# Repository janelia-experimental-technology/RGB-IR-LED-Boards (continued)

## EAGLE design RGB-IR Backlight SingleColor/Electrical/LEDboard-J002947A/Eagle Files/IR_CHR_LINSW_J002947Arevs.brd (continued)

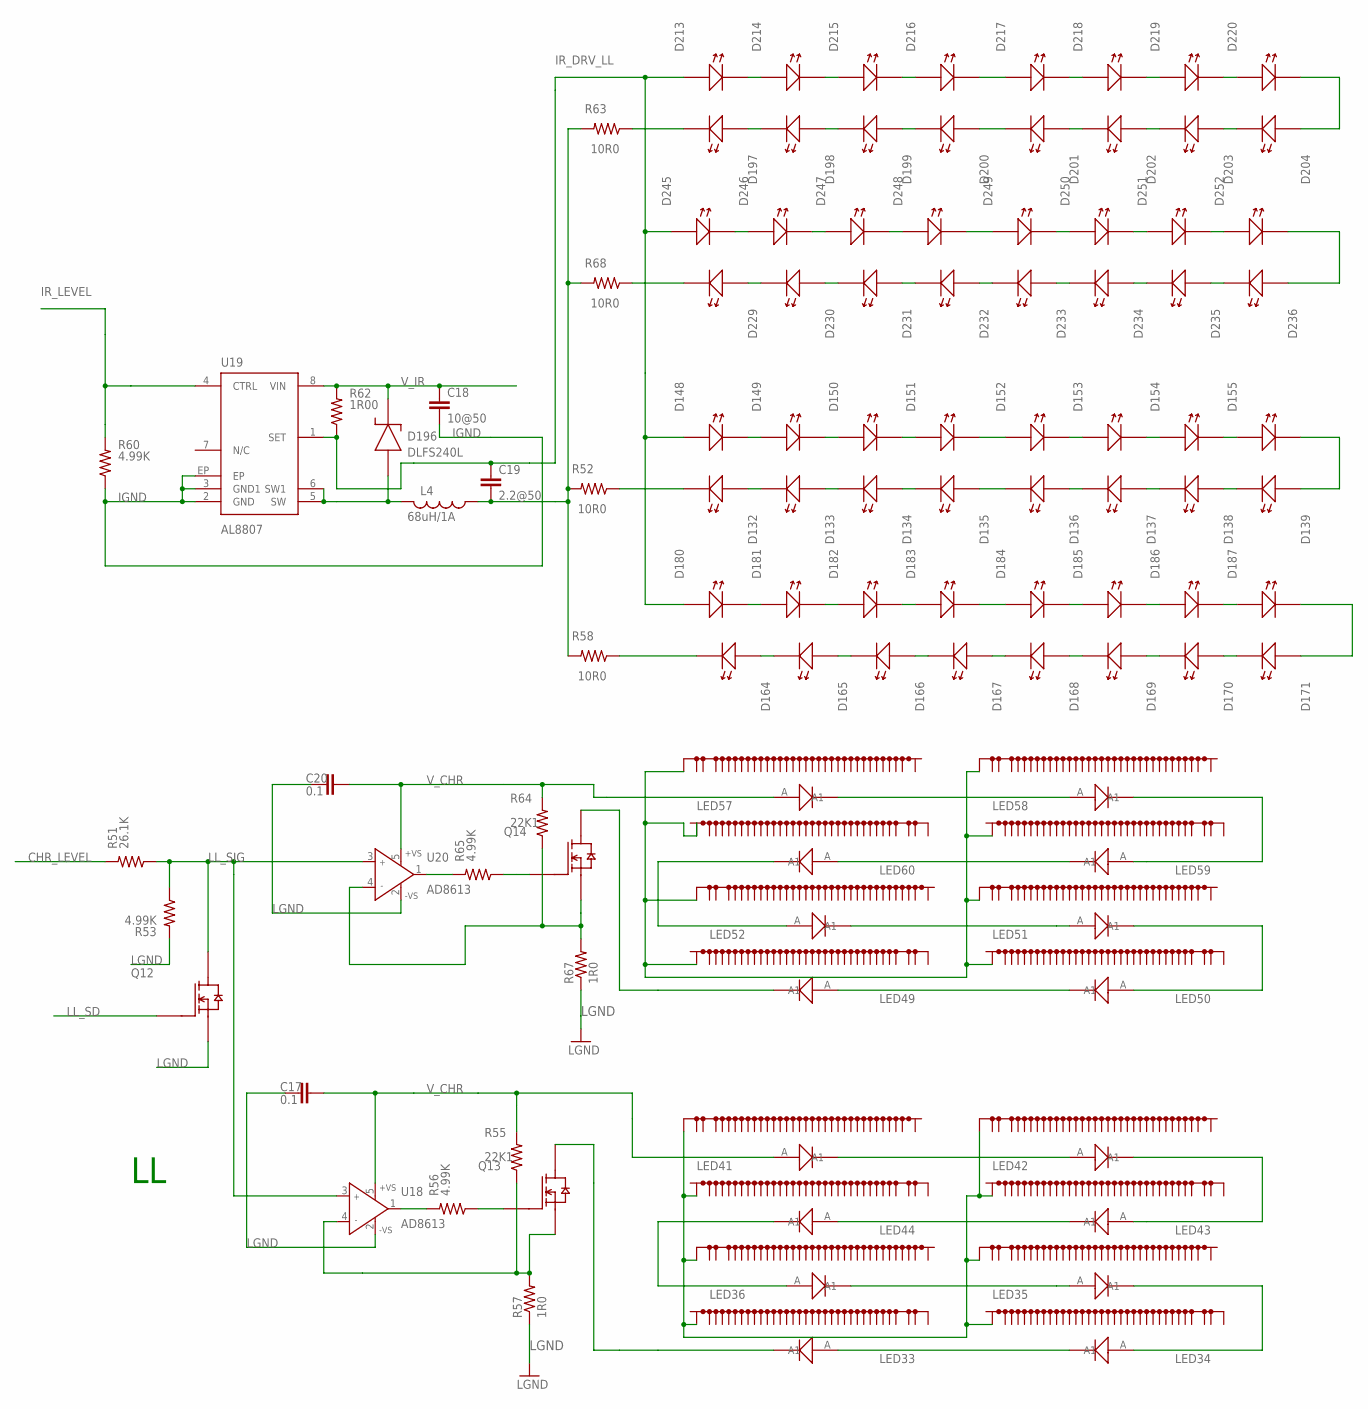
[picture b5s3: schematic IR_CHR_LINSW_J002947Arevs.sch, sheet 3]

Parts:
C17, C20: 0.1; 0603S
C18: 10@50; 1206S
C19: 2.2@50; 1206S
D132, D133, D134, D135, D136, D137, D138, D148, D149, D150, D151, D152, D153, D154, D155, D164, D165, D166, D167, D168, D169, D170, D171, D180, D181, D182, D183, D184, D185, D186, D187, D197, D198, D199, D200, D201, D202, D203, D204, D213, D214, D215, D216, D217, D218, D219, D220, D229, D230, D231, D232, D233, D234, D235, D236, D245, D246, D247, D248, D249, D250, D251, D252: LEDLED_SFH4050_HEAT; LED_SFH4050_HEAT
D139: LEDLED_SFH4050_C; LED_SFH4050_HEAT_C
D196: DLFS240L; PWRDI-123
L4: 68uH/1A; SRU8043
LED33, LED34, LED35, LED36, LED41, LED42, LED43, LED44, LED49, LED50, LED51, LED52, LED57, LED58, LED59, LED60: REBEL_0603OG_LED_W0603_EVEN_12; OG_LED_W0603_EVEN_12
Q12: MOSFET-N; SC-70
Q13, Q14: MOSFET-NTI252_HS; TO252_HS
R51: 26.1K; 0603S
R52, R58, R63, R68: 10R0; 1206S
R53, R56, R65: 4.99K; 0603S
R55, R64: 22K1; 0805S
R57, R67: 1R0; 2512WIDE_HS1
R60: 4.99K; 0805S
R62: 1R00; 1206S
U18, U20: AD8613; SOT23-5
U19: AL8807; MSOP8-EP

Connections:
CHR_LEVEL: R51.2; also elsewhere on the board
IGND: C18.2, R60.1, U19.2 (GND), U19.3 (GND1), U19.EP; also elsewhere on the board
IR_DRV_LL: C19.1, D148.A, D148.A1 (A), D180.A, D180.A1 (A), D213.A, D213.A1 (A), D245.A, D245.A1 (A), R62.1, U19.1 (SET)
IR_LEVEL: R60.2, U19.4 (CTRL); also elsewhere on the board
IR_RET_LL: C19.2, L4.1, R52.2, R58.2, R63.2, R68.2
LGND: C17.2, C20.2, Q12.2 (S), R53.2, R57.1, R57.1A (1), R57.1A1 (1), R57.1B (1), R57.1B1 (1), R57.1C (1), R67.1, R67.1A (1), R67.1A1 (1), R67.1B (1), R67.1B1 (1), R67.1C (1), U18.2 (-VS), U20.2 (-VS); also elsewhere on the board
LL_SD: Q12.1 (G); also elsewhere on the board
LL_SIG: Q12.3 (D), R51.1, R53.1, U18.3 (IN+), U20.3 (IN+)
unnamed: D196.A, L4.2, U19.5 (SW), U19.6 (SW1)
unnamed: D203.A, D203.A1 (A), D204.C (K), D204.C1 (K)
unnamed: Q14.1 (G), R65.1
unnamed: D202.A, D202.A1 (A), D203.C (K), D203.C1 (K)
unnamed: Q13.1 (G), R56.1
unnamed: R65.2, U20.1 (OUT)
unnamed: D201.A, D201.A1 (A), D202.C (K), D202.C1 (K)
unnamed: D199.A, D199.A1 (A), D200.C (K), D200.C1 (K)
unnamed: D198.A, D198.A1 (A), D199.C (K), D199.C1 (K)
unnamed: D197.A, D197.A1 (A), D198.C (K), D198.C1 (K)
unnamed: D213.C (K), D213.C1 (K), D214.A, D214.A1 (A)
unnamed: D214.C (K), D214.C1 (K), D215.A, D215.A1 (A)
unnamed: D215.C (K), D215.C1 (K), D216.A, D216.A1 (A)
unnamed: D200.A, D200.A1 (A), D201.C (K), D201.C1 (K)
unnamed: D235.A, D235.A1 (A), D236.C (K), D236.C1 (K)
unnamed: D234.A, D234.A1 (A), D235.C (K), D235.C1 (K)
unnamed: D233.A, D233.A1 (A), D234.C (K), D234.C1 (K)
unnamed: D232.A, D232.A1 (A), D233.C (K), D233.C1 (K)
unnamed: D231.A, D231.A1 (A), D232.C (K), D232.C1 (K)
unnamed: D230.A, D230.A1 (A), D231.C (K), D231.C1 (K)
unnamed: D229.A, D229.A1 (A), D230.C (K), D230.C1 (K)
unnamed: D217.C (K), D217.C1 (K), D218.A, D218.A1 (A)
unnamed: D218.C (K), D218.C1 (K), D219.A, D219.A1 (A)
unnamed: D219.C (K), D219.C1 (K), D220.A, D220.A1 (A)
unnamed: D245.C (K), D245.C1 (K), D246.A, D246.A1 (A)
unnamed: D246.C (K), D246.C1 (K), D247.A, D247.A1 (A)
unnamed: D247.C (K), D247.C1 (K), D248.A, D248.A1 (A)
unnamed: D249.C (K), D249.C1 (K), D250.A, D250.A1 (A)
unnamed: D250.C (K), D250.C1 (K), D251.A, D251.A1 (A)
unnamed: D251.C (K), D251.C1 (K), D252.A, D252.A1 (A)
unnamed: D216.C (K), D216.C1 (K), D217.A, D217.A1 (A)
unnamed: D204.A, D204.A1 (A), D220.C (K), D220.C1 (K)
unnamed: D248.C (K), D248.C1 (K), D249.A, D249.A1 (A)
unnamed: D236.A, D236.A1 (A), D252.C (K), D252.C1 (K)
unnamed: Q13.2 (S), R55.1, R57.2, U18.4 (IN-)
unnamed: LED57.C (K1), LED58.A (A1)
unnamed: LED58.C (K1), LED59.A (A1)
unnamed: LED59.C (K1), LED60.A (A1)
unnamed: LED52.A (A1), LED60.C (K1)
unnamed: LED51.A (A1), LED52.C (K1)
unnamed: LED50.A (A1), LED51.C (K1)
unnamed: R56.2, U18.1 (OUT)
unnamed: LED49.A (A1), LED50.C (K1)
unnamed: Q14.2 (S), R64.1, R67.2, U20.4 (IN-)
unnamed: D138.A, D138.A1 (A), D139.C (K), D139.C1 (K)
unnamed: D137.A, D137.A1 (A), D138.C (K), D138.C1 (K)
unnamed: D136.A, D136.A1 (A), D137.C (K), D137.C1 (K)
unnamed: D134.A, D134.A1 (A), D135.C (K), D135.C1 (K)
unnamed: D133.A, D133.A1 (A), D134.C (K), D134.C1 (K)
unnamed: D132.A, D132.A1 (A), D133.C (K), D133.C1 (K)
unnamed: D148.C (K), D148.C1 (K), D149.A, D149.A1 (A)
unnamed: D149.C (K), D149.C1 (K), D150.A, D150.A1 (A)
unnamed: D150.C (K), D150.C1 (K), D151.A, D151.A1 (A)
unnamed: D135.A, D135.A1 (A), D136.C (K), D136.C1 (K)
unnamed: D170.A, D170.A1 (A), D171.C (K), D171.C1 (K)
unnamed: D169.A, D169.A1 (A), D170.C (K), D170.C1 (K)
unnamed: D168.A, D168.A1 (A), D169.C (K), D169.C1 (K)
unnamed: D167.A, D167.A1 (A), D168.C (K), D168.C1 (K)
unnamed: D166.A, D166.A1 (A), D167.C (K), D167.C1 (K)
unnamed: D165.A, D165.A1 (A), D166.C (K), D166.C1 (K)
unnamed: D164.A, D164.A1 (A), D165.C (K), D165.C1 (K)
unnamed: D152.C (K), D152.C1 (K), D153.A, D153.A1 (A)
unnamed: D153.C (K), D153.C1 (K), D154.A, D154.A1 (A)
unnamed: D154.C (K), D154.C1 (K), D155.A, D155.A1 (A)
unnamed: D180.C (K), D180.C1 (K), D181.A, D181.A1 (A)
unnamed: D181.C (K), D181.C1 (K), D182.A, D182.A1 (A)
unnamed: D182.C (K), D182.C1 (K), D183.A, D183.A1 (A)
unnamed: D184.C (K), D184.C1 (K), D185.A, D185.A1 (A)
unnamed: D185.C (K), D185.C1 (K), D186.A, D186.A1 (A)
unnamed: D186.C (K), D186.C1 (K), D187.A, D187.A1 (A)
unnamed: D151.C (K), D151.C1 (K), D152.A, D152.A1 (A)
unnamed: D139.A, D155.C (K), D155.C1 (K)
unnamed: D183.C (K), D183.C1 (K), D184.A, D184.A1 (A)
unnamed: D171.A, D171.A1 (A), D187.C (K), D187.C1 (K)
unnamed: LED41.C (K1), LED42.A (A1)
unnamed: LED42.C (K1), LED43.A (A1)
unnamed: LED43.C (K1), LED44.A (A1)
unnamed: LED36.A (A1), LED44.C (K1)
unnamed: LED35.A (A1), LED36.C (K1)
unnamed: LED34.A (A1), LED35.C (K1)
unnamed: LED33.A (A1), LED34.C (K1)
unnamed: D132.C (K), D132.C1 (K), R52.1
unnamed: D164.C (K), D164.C1 (K), R58.1
unnamed: D197.C (K), D197.C1 (K), R63.1
unnamed: D229.C (K), D229.C1 (K), R68.1
Q14: LED33.C (K1), Q13.3 (D), Q13.3S (D), Q13.P$1 (D), Q13.P$2 (D), Q13.P$3 (D), Q13.P$4 (D), Q13.P$5 (D), Q13.P$6 (D), Q13.P$7 (D), Q13.P$8 (D), Q13.P$9 (D), Q13.P$10 (D), Q13.P$11 (D), Q13.P$12 (D)
Q16: LED49.C (K1), Q14.3 (D), Q14.3S (D), Q14.P$1 (D), Q14.P$2 (D), Q14.P$3 (D), Q14.P$4 (D), Q14.P$5 (D), Q14.P$6 (D), Q14.P$7 (D), Q14.P$8 (D), Q14.P$9 (D), Q14.P$10 (D), Q14.P$11 (D), Q14.P$12 (D)
TH: LED33.TH1 (TH), LED33.TH@38 (TH), LED33.TH@39 (TH), LED33.TH@40 (TH), LED33.TH@41 (TH), LED33.TH@42 (TH), LED33.TH@43 (TH), LED33.TH@44 (TH), LED33.TH@45 (TH), LED33.TH@46 (TH), LED33.TH@47 (TH), LED33.TH@48 (TH), LED33.TH@49 (TH), LED33.TH@50 (TH), LED33.TH@51 (TH), LED33.TH@52 (TH), LED33.TH@53 (TH), LED33.TH@54 (TH), LED33.TH@55 (TH), LED33.TH@56 (TH), LED33.TH@57 (TH), LED33.TH@58 (TH), LED33.TH@59 (TH), LED33.TH@60 (TH), LED33.TH@61 (TH), LED33.TH@62 (TH), LED33.TH@63 (TH), LED33.TH@64 (TH), LED33.TH@65 (TH), LED33.TH@66 (TH), LED33.TH@67 (TH), LED33.TH@68 (TH), LED33.TH@69 (TH), LED33.TH@70 (TH), LED34.TH1 (TH), LED34.TH@38 (TH), LED34.TH@39 (TH), LED34.TH@40 (TH), LED34.TH@41 (TH), LED34.TH@42 (TH), LED34.TH@43 (TH), LED34.TH@44 (TH), LED34.TH@45 (TH), LED34.TH@46 (TH), LED34.TH@47 (TH), LED34.TH@48 (TH), LED34.TH@49 (TH), LED34.TH@50 (TH), LED34.TH@51 (TH), LED34.TH@52 (TH), LED34.TH@53 (TH), LED34.TH@54 (TH), LED34.TH@55 (TH), LED34.TH@56 (TH), LED34.TH@57 (TH), LED34.TH@58 (TH), LED34.TH@59 (TH), LED34.TH@60 (TH), LED34.TH@61 (TH), LED34.TH@62 (TH), LED34.TH@63 (TH), LED34.TH@64 (TH), LED34.TH@65 (TH), LED34.TH@66 (TH), LED34.TH@67 (TH), LED34.TH@68 (TH), LED34.TH@69 (TH), LED34.TH@70 (TH), LED35.TH1 (TH), LED35.TH@38 (TH), LED35.TH@39 (TH), LED35.TH@40 (TH), LED35.TH@41 (TH), LED35.TH@42 (TH), LED35.TH@43 (TH), LED35.TH@44 (TH), LED35.TH@45 (TH), LED35.TH@46 (TH), LED35.TH@47 (TH), LED35.TH@48 (TH), LED35.TH@49 (TH), LED35.TH@50 (TH), LED35.TH@51 (TH), LED35.TH@52 (TH), LED35.TH@53 (TH), LED35.TH@54 (TH), LED35.TH@55 (TH), LED35.TH@56 (TH), LED35.TH@57 (TH), LED35.TH@58 (TH), LED35.TH@59 (TH), LED35.TH@60 (TH), LED35.TH@61 (TH), LED35.TH@62 (TH), LED35.TH@63 (TH), LED35.TH@64 (TH), LED35.TH@65 (TH), LED35.TH@66 (TH), LED35.TH@67 (TH), LED35.TH@68 (TH), LED35.TH@69 (TH), LED35.TH@70 (TH), LED36.TH1 (TH), LED36.TH@38 (TH), LED36.TH@39 (TH), LED36.TH@40 (TH), LED36.TH@41 (TH), LED36.TH@42 (TH), LED36.TH@43 (TH), LED36.TH@44 (TH), LED36.TH@45 (TH), LED36.TH@46 (TH), LED36.TH@47 (TH), LED36.TH@48 (TH), LED36.TH@49 (TH), LED36.TH@50 (TH), LED36.TH@51 (TH), LED36.TH@52 (TH), LED36.TH@53 (TH), LED36.TH@54 (TH), LED36.TH@55 (TH), LED36.TH@56 (TH), LED36.TH@57 (TH), LED36.TH@58 (TH), LED36.TH@59 (TH), LED36.TH@60 (TH), LED36.TH@61 (TH), LED36.TH@62 (TH), LED36.TH@63 (TH), LED36.TH@64 (TH), LED36.TH@65 (TH), LED36.TH@66 (TH), LED36.TH@67 (TH), LED36.TH@68 (TH), LED36.TH@69 (TH), LED36.TH@70 (TH), LED41.TH1 (TH), LED41.TH@38 (TH), LED41.TH@39 (TH), LED41.TH@40 (TH), LED41.TH@41 (TH), LED41.TH@42 (TH), LED41.TH@43 (TH), LED41.TH@44 (TH), LED41.TH@45 (TH), LED41.TH@46 (TH), LED41.TH@47 (TH), LED41.TH@48 (TH), LED41.TH@49 (TH), LED41.TH@50 (TH), LED41.TH@51 (TH), LED41.TH@52 (TH), LED41.TH@53 (TH), LED41.TH@54 (TH), LED41.TH@55 (TH), LED41.TH@56 (TH), LED41.TH@57 (TH), LED41.TH@58 (TH), LED41.TH@59 (TH), LED41.TH@60 (TH), LED41.TH@61 (TH), LED41.TH@62 (TH), LED41.TH@63 (TH), LED41.TH@64 (TH), LED41.TH@65 (TH), LED41.TH@66 (TH), LED41.TH@67 (TH), LED41.TH@68 (TH), LED41.TH@69 (TH), LED41.TH@70 (TH), LED42.TH1 (TH), LED42.TH@38 (TH), LED42.TH@39 (TH), LED42.TH@40 (TH), LED42.TH@41 (TH), LED42.TH@42 (TH), LED42.TH@43 (TH), LED42.TH@44 (TH), LED42.TH@45 (TH), LED42.TH@46 (TH), LED42.TH@47 (TH), LED42.TH@48 (TH), LED42.TH@49 (TH), LED42.TH@50 (TH), LED42.TH@51 (TH), LED42.TH@52 (TH), LED42.TH@53 (TH), LED42.TH@54 (TH), LED42.TH@55 (TH), LED42.TH@56 (TH), LED42.TH@57 (TH), LED42.TH@58 (TH), LED42.TH@59 (TH), LED42.TH@60 (TH), LED42.TH@61 (TH), LED42.TH@62 (TH), LED42.TH@63 (TH), LED42.TH@64 (TH)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; also elsewhere on the board
V_CHR: C17.1, C20.1, LED41.A (A1), LED57.A (A1), R55.2, R64.2, U18.5 (+VS), U20.5 (+VS); also elsewhere on the board
V_IR: C18.1, D196.K, R62.2, U19.8 (VIN); also elsewhere on the board

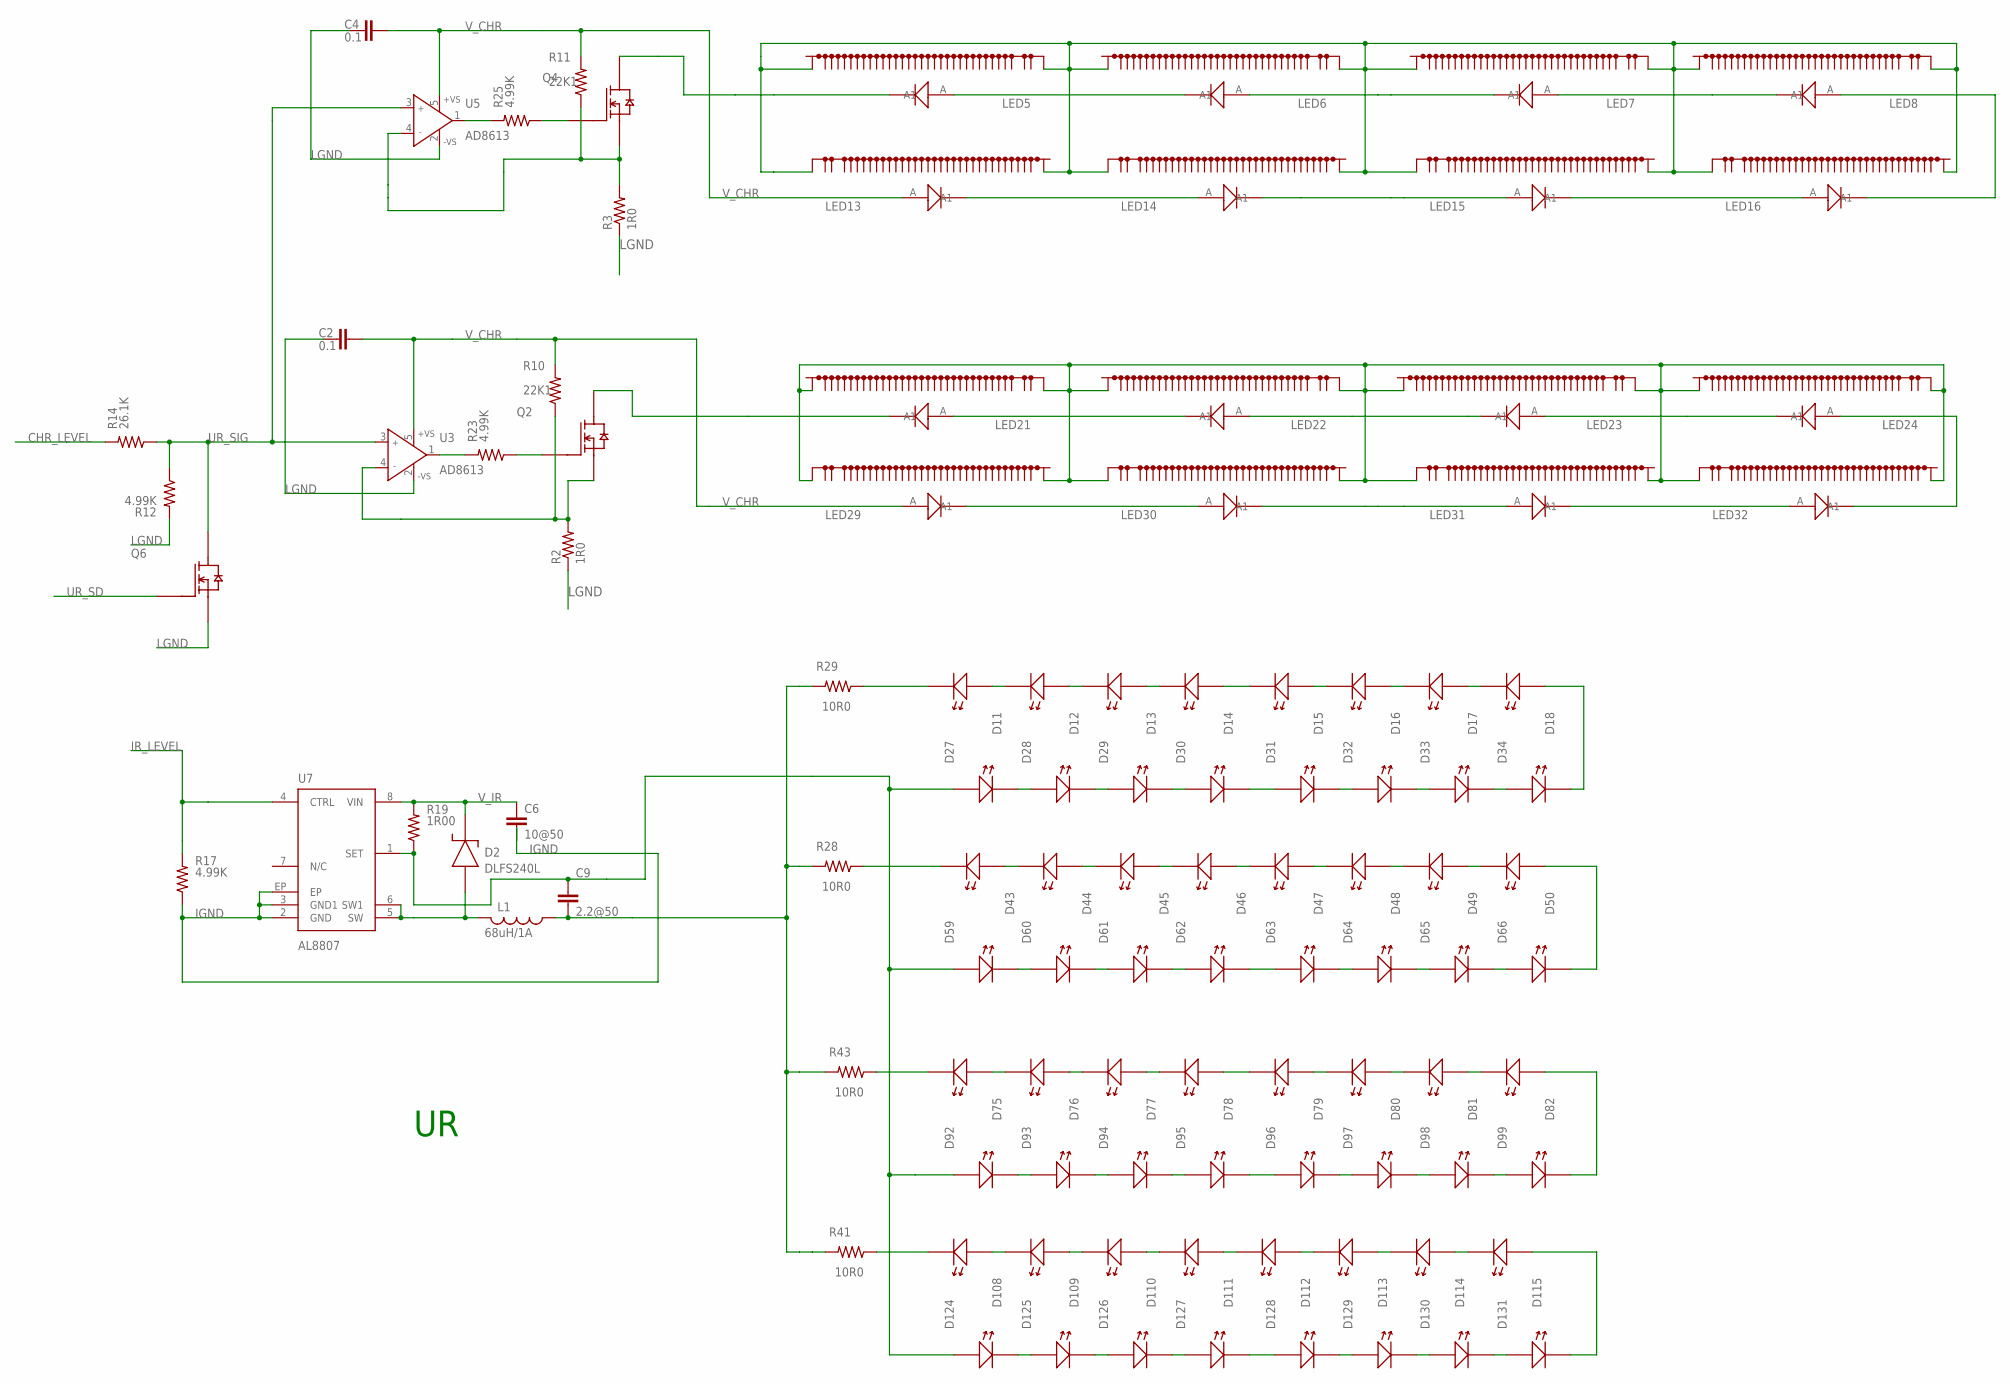
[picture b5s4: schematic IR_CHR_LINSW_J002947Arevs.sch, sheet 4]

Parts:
C2, C4: 0.1; 0603S
C6: 10@50; 1206S
C9: 2.2@50; 1206S
D2: DLFS240L; PWRDI-123
D11, D12, D13, D14, D15, D16, D17, D18, D27, D28, D29, D30, D31, D32, D33, D34, D43, D44, D45, D46, D47, D48, D49, D50, D59, D60, D61, D62, D63, D64, D65, D66, D75, D76, D77, D78, D79, D80, D81, D82, D92, D93, D94, D95, D96, D97, D98, D99, D108, D109, D110, D111, D112, D113, D114, D115, D124, D125, D126, D127, D128, D129, D130, D131: LEDLED_SFH4050_HEAT; LED_SFH4050_HEAT
L1: 68uH/1A; SRU8043
LED5, LED6, LED7, LED8, LED13, LED14, LED15, LED16, LED21, LED22, LED23, LED24, LED29, LED30, LED31, LED32: REBEL_0603OG_LED_W0603_EVEN_12; OG_LED_W0603_EVEN_12
Q2, Q4: MOSFET-NTI252_HS; TO252_HS
Q6: MOSFET-N; SC-70
R2, R3: 1R0; 2512WIDE_HS1
R10, R11: 22K1; 0805S
R12, R23, R25: 4.99K; 0603S
R14: 26.1K; 0603S
R17: 4.99K; 0805S
R19: 1R00; 1206S
R28, R29, R41, R43: 10R0; 1206S
U3, U5: AD8613; SOT23-5
U7: AL8807; MSOP8-EP

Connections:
CHR_LEVEL: R14.2; also elsewhere on the board
IGND: C6.2, R17.1, U7.2 (GND), U7.3 (GND1), U7.EP; also elsewhere on the board
IR_DRV_UR: C9.1, D27.A, D27.A1 (A), D59.A, D59.A1 (A), D92.A, D92.A1 (A), D124.A, D124.A1 (A), R19.1, U7.1 (SET)
IR_LEVEL: R17.2, U7.4 (CTRL); also elsewhere on the board
IR_RET_UR: C9.2, L1.1, R28.2, R29.2, R41.2, R43.2
LGND: C2.2, C4.2, Q6.2 (S), R2.1, R2.1A (1), R2.1A1 (1), R2.1B (1), R2.1B1 (1), R2.1C (1), R3.1, R3.1A (1), R3.1A1 (1), R3.1B (1), R3.1B1 (1), R3.1C (1), R12.2, U3.2 (-VS), U5.2 (-VS); also elsewhere on the board
unnamed: Q4.2 (S), R3.2, R11.1, U5.4 (IN-)
unnamed: D2.A, L1.2, U7.5 (SW), U7.6 (SW1)
unnamed: Q4.1 (G), R25.1
unnamed: R25.2, U5.1 (OUT)
unnamed: Q2.2 (S), R2.2, R10.1, U3.4 (IN-)
unnamed: R23.2, U3.1 (OUT)
unnamed: Q2.1 (G), R23.1
unnamed: D81.A, D81.A1 (A), D82.C (K), D82.C1 (K)
unnamed: D80.A, D80.A1 (A), D81.C (K), D81.C1 (K)
unnamed: D79.A, D79.A1 (A), D80.C (K), D80.C1 (K)
unnamed: D77.A, D77.A1 (A), D78.C (K), D78.C1 (K)
unnamed: D76.A, D76.A1 (A), D77.C (K), D77.C1 (K)
unnamed: D75.A, D75.A1 (A), D76.C (K), D76.C1 (K)
unnamed: D92.C (K), D92.C1 (K), D93.A, D93.A1 (A)
unnamed: D114.A, D114.A1 (A), D115.C (K), D115.C1 (K)
unnamed: D113.A, D113.A1 (A), D114.C (K), D114.C1 (K)
unnamed: D112.A, D112.A1 (A), D113.C (K), D113.C1 (K)
unnamed: D111.A, D111.A1 (A), D112.C (K), D112.C1 (K)
unnamed: D110.A, D110.A1 (A), D111.C (K), D111.C1 (K)
unnamed: D109.A, D109.A1 (A), D110.C (K), D110.C1 (K)
unnamed: D108.A, D108.A1 (A), D109.C (K), D109.C1 (K)
unnamed: D96.C (K), D96.C1 (K), D97.A, D97.A1 (A)
unnamed: D97.C (K), D97.C1 (K), D98.A, D98.A1 (A)
unnamed: D98.C (K), D98.C1 (K), D99.A, D99.A1 (A)
unnamed: D124.C (K), D124.C1 (K), D125.A, D125.A1 (A)
unnamed: D126.C (K), D126.C1 (K), D127.A, D127.A1 (A)
unnamed: D128.C (K), D128.C1 (K), D129.A, D129.A1 (A)
unnamed: D129.C (K), D129.C1 (K), D130.A, D130.A1 (A)
unnamed: D130.C (K), D130.C1 (K), D131.A, D131.A1 (A)
unnamed: D82.A, D82.A1 (A), D99.C (K), D99.C1 (K)
unnamed: D127.C (K), D127.C1 (K), D128.A, D128.A1 (A)
unnamed: D115.A, D115.A1 (A), D131.C (K), D131.C1 (K)
unnamed: D49.A, D49.A1 (A), D50.C (K), D50.C1 (K)
unnamed: D46.A, D46.A1 (A), D47.C (K), D47.C1 (K)
unnamed: D45.A, D45.A1 (A), D46.C (K), D46.C1 (K)
unnamed: D44.A, D44.A1 (A), D45.C (K), D45.C1 (K)
unnamed: D43.A, D43.A1 (A), D44.C (K), D44.C1 (K)
unnamed: D31.C (K), D31.C1 (K), D32.A, D32.A1 (A)
unnamed: D59.C (K), D59.C1 (K), D60.A, D60.A1 (A)
unnamed: D17.A, D17.A1 (A), D18.C (K), D18.C1 (K)
unnamed: D16.A, D16.A1 (A), D17.C (K), D17.C1 (K)
unnamed: D15.A, D15.A1 (A), D16.C (K), D16.C1 (K)
unnamed: D13.A, D13.A1 (A), D14.C (K), D14.C1 (K)
unnamed: D12.A, D12.A1 (A), D13.C (K), D13.C1 (K)
unnamed: D30.C (K), D30.C1 (K), D31.A, D31.A1 (A)
unnamed: D18.A, D18.A1 (A), D34.C (K), D34.C1 (K)
unnamed: D28.C (K), D28.C1 (K), D29.A, D29.A1 (A)
unnamed: D50.A, D50.A1 (A), D66.C (K), D66.C1 (K)
unnamed: D47.A, D47.A1 (A), D48.C (K), D48.C1 (K)
unnamed: D125.C (K), D125.C1 (K), D126.A, D126.A1 (A)
unnamed: D95.C (K), D95.C1 (K), D96.A, D96.A1 (A)
unnamed: D33.C (K), D33.C1 (K), D34.A, D34.A1 (A)
unnamed: D78.A, D78.A1 (A), D79.C (K), D79.C1 (K)
unnamed: LED31.C (K1), LED32.A (A1)
unnamed: LED24.A (A1), LED32.C (K1)
unnamed: LED21.A (A1), LED22.C (K1)
unnamed: LED22.A (A1), LED23.C (K1)
unnamed: LED23.A (A1), LED24.C (K1)
unnamed: LED15.C (K1), LED16.A (A1)
unnamed: LED8.A (A1), LED16.C (K1)
unnamed: LED14.C (K1), LED15.A (A1)
unnamed: LED13.C (K1), LED14.A (A1)
unnamed: LED6.A (A1), LED7.C (K1)
unnamed: D11.C (K), D11.C1 (K), R29.1
unnamed: D43.C (K), D43.C1 (K), R28.1
unnamed: D75.C (K), D75.C1 (K), R43.1
unnamed: D108.C (K), D108.C1 (K), R41.1
unnamed: D93.C (K), D93.C1 (K), D94.A, D94.A1 (A)
unnamed: D94.C (K), D94.C1 (K), D95.A, D95.A1 (A)
unnamed: D48.A, D48.A1 (A), D49.C (K), D49.C1 (K)
unnamed: D32.C (K), D32.C1 (K), D33.A, D33.A1 (A)
unnamed: D14.A, D14.A1 (A), D15.C (K), D15.C1 (K)
unnamed: D11.A, D11.A1 (A), D12.C (K), D12.C1 (K)
unnamed: D27.C (K), D27.C1 (K), D28.A, D28.A1 (A)
unnamed: D29.C (K), D29.C1 (K), D30.A, D30.A1 (A)
unnamed: D60.C (K), D60.C1 (K), D61.A, D61.A1 (A)
unnamed: D61.C (K), D61.C1 (K), D62.A, D62.A1 (A)
unnamed: D62.C (K), D62.C1 (K), D63.A, D63.A1 (A)
unnamed: D63.C (K), D63.C1 (K), D64.A, D64.A1 (A)
unnamed: D64.C (K), D64.C1 (K), D65.A, D65.A1 (A)
unnamed: D65.C (K), D65.C1 (K), D66.A, D66.A1 (A)
unnamed: LED30.C (K1), LED31.A (A1)
unnamed: LED29.C (K1), LED30.A (A1)
unnamed: LED5.A (A1), LED6.C (K1)
unnamed: LED7.A (A1), LED8.C (K1)
Q5: LED21.C (K1), Q2.3 (D), Q2.3S (D), Q2.P$1 (D), Q2.P$2 (D), Q2.P$3 (D), Q2.P$4 (D), Q2.P$5 (D), Q2.P$6 (D), Q2.P$7 (D), Q2.P$8 (D), Q2.P$9 (D), Q2.P$10 (D), Q2.P$11 (D), Q2.P$12 (D)
Q7: LED5.C (K1), Q4.3 (D), Q4.3S (D), Q4.P$1 (D), Q4.P$2 (D), Q4.P$3 (D), Q4.P$4 (D), Q4.P$5 (D), Q4.P$6 (D), Q4.P$7 (D), Q4.P$8 (D), Q4.P$9 (D), Q4.P$10 (D), Q4.P$11 (D), Q4.P$12 (D)
TH: LED5.TH1 (TH), LED5.TH@38 (TH), LED5.TH@39 (TH), LED5.TH@40 (TH), LED5.TH@41 (TH), LED5.TH@42 (TH), LED5.TH@43 (TH), LED5.TH@44 (TH), LED5.TH@45 (TH), LED5.TH@46 (TH), LED5.TH@47 (TH), LED5.TH@48 (TH), LED5.TH@49 (TH), LED5.TH@50 (TH), LED5.TH@51 (TH), LED5.TH@52 (TH), LED5.TH@53 (TH), LED5.TH@54 (TH), LED5.TH@55 (TH), LED5.TH@56 (TH), LED5.TH@57 (TH), LED5.TH@58 (TH), LED5.TH@59 (TH), LED5.TH@60 (TH), LED5.TH@61 (TH), LED5.TH@62 (TH), LED5.TH@63 (TH), LED5.TH@64 (TH), LED5.TH@65 (TH), LED5.TH@66 (TH), LED5.TH@67 (TH), LED5.TH@68 (TH), LED5.TH@69 (TH), LED5.TH@70 (TH), LED6.TH1 (TH), LED6.TH@38 (TH), LED6.TH@39 (TH), LED6.TH@40 (TH), LED6.TH@41 (TH), LED6.TH@42 (TH), LED6.TH@43 (TH), LED6.TH@44 (TH), LED6.TH@45 (TH), LED6.TH@46 (TH), LED6.TH@47 (TH), LED6.TH@48 (TH), LED6.TH@49 (TH), LED6.TH@50 (TH), LED6.TH@51 (TH), LED6.TH@52 (TH), LED6.TH@53 (TH), LED6.TH@54 (TH), LED6.TH@55 (TH), LED6.TH@56 (TH), LED6.TH@57 (TH), LED6.TH@58 (TH), LED6.TH@59 (TH), LED6.TH@60 (TH), LED6.TH@61 (TH), LED6.TH@62 (TH), LED6.TH@63 (TH), LED6.TH@64 (TH), LED6.TH@65 (TH), LED6.TH@66 (TH), LED6.TH@67 (TH), LED6.TH@68 (TH), LED6.TH@69 (TH), LED6.TH@70 (TH), LED7.TH1 (TH), LED7.TH@38 (TH), LED7.TH@39 (TH), LED7.TH@40 (TH), LED7.TH@41 (TH), LED7.TH@42 (TH), LED7.TH@43 (TH), LED7.TH@44 (TH), LED7.TH@45 (TH), LED7.TH@46 (TH), LED7.TH@47 (TH), LED7.TH@48 (TH), LED7.TH@49 (TH), LED7.TH@50 (TH), LED7.TH@51 (TH), LED7.TH@52 (TH), LED7.TH@53 (TH), LED7.TH@54 (TH), LED7.TH@55 (TH), LED7.TH@56 (TH), LED7.TH@57 (TH), LED7.TH@58 (TH), LED7.TH@59 (TH), LED7.TH@60 (TH), LED7.TH@61 (TH), LED7.TH@62 (TH), LED7.TH@63 (TH), LED7.TH@64 (TH), LED7.TH@65 (TH), LED7.TH@66 (TH), LED7.TH@67 (TH), LED7.TH@68 (TH), LED7.TH@69 (TH), LED7.TH@70 (TH), LED8.TH1 (TH), LED8.TH@38 (TH), LED8.TH@39 (TH), LED8.TH@40 (TH), LED8.TH@41 (TH), LED8.TH@42 (TH), LED8.TH@43 (TH), LED8.TH@44 (TH), LED8.TH@45 (TH), LED8.TH@46 (TH), LED8.TH@47 (TH), LED8.TH@48 (TH), LED8.TH@49 (TH), LED8.TH@50 (TH), LED8.TH@51 (TH), LED8.TH@52 (TH), LED8.TH@53 (TH), LED8.TH@54 (TH), LED8.TH@55 (TH), LED8.TH@56 (TH), LED8.TH@57 (TH), LED8.TH@58 (TH), LED8.TH@59 (TH), LED8.TH@60 (TH), LED8.TH@61 (TH), LED8.TH@62 (TH), LED8.TH@63 (TH), LED8.TH@64 (TH), LED8.TH@65 (TH), LED8.TH@66 (TH), LED8.TH@67 (TH), LED8.TH@68 (TH), LED8.TH@69 (TH), LED8.TH@70 (TH), LED13.TH1 (TH), LED13.TH@38 (TH), LED13.TH@39 (TH), LED13.TH@40 (TH), LED13.TH@41 (TH), LED13.TH@42 (TH), LED13.TH@43 (TH), LED13.TH@44 (TH), LED13.TH@45 (TH), LED13.TH@46 (TH), LED13.TH@47 (TH), LED13.TH@48 (TH), LED13.TH@49 (TH), LED13.TH@50 (TH), LED13.TH@51 (TH), LED13.TH@52 (TH), LED13.TH@53 (TH), LED13.TH@54 (TH), LED13.TH@55 (TH), LED13.TH@56 (TH), LED13.TH@57 (TH), LED13.TH@58 (TH), LED13.TH@59 (TH), LED13.TH@60 (TH), LED13.TH@61 (TH), LED13.TH@62 (TH), LED13.TH@63 (TH), LED13.TH@64 (TH), LED13.TH@65 (TH), LED13.TH@66 (TH), LED13.TH@67 (TH), LED13.TH@68 (TH), LED13.TH@69 (TH), LED13.TH@70 (TH), LED14.TH1 (TH), LED14.TH@38 (TH), LED14.TH@39 (TH), LED14.TH@40 (TH), LED14.TH@41 (TH), LED14.TH@42 (TH), LED14.TH@43 (TH), LED14.TH@44 (TH), LED14.TH@45 (TH), LED14.TH@46 (TH), LED14.TH@47 (TH), LED14.TH@48 (TH), LED14.TH@49 (TH), LED14.TH@50 (TH), LED14.TH@51 (TH), LED14.TH@52 (TH), LED14.TH@53 (TH), LED14.TH@54 (TH), LED14.TH@55 (TH), LED14.TH@56 (TH), LED14.TH@57 (TH), LED14.TH@58 (TH), LED14.TH@59 (TH), LED14.TH@60 (TH), LED14.TH@61 (TH), LED14.TH@62 (TH), LED14.TH@63 (TH), LED14.TH@64 (TH)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; also elsewhere on the board
UR_SD: Q6.1 (G); also elsewhere on the board
UR_SIG: Q6.3 (D), R12.1, R14.1, U3.3 (IN+), U5.3 (IN+)
V_CHR: C2.1, C4.1, LED13.A (A1), LED29.A (A1), R10.2, R11.2, U3.5 (+VS), U5.5 (+VS); also elsewhere on the board
V_IR: C6.1, D2.K, R19.2, U7.8 (VIN); also elsewhere on the board

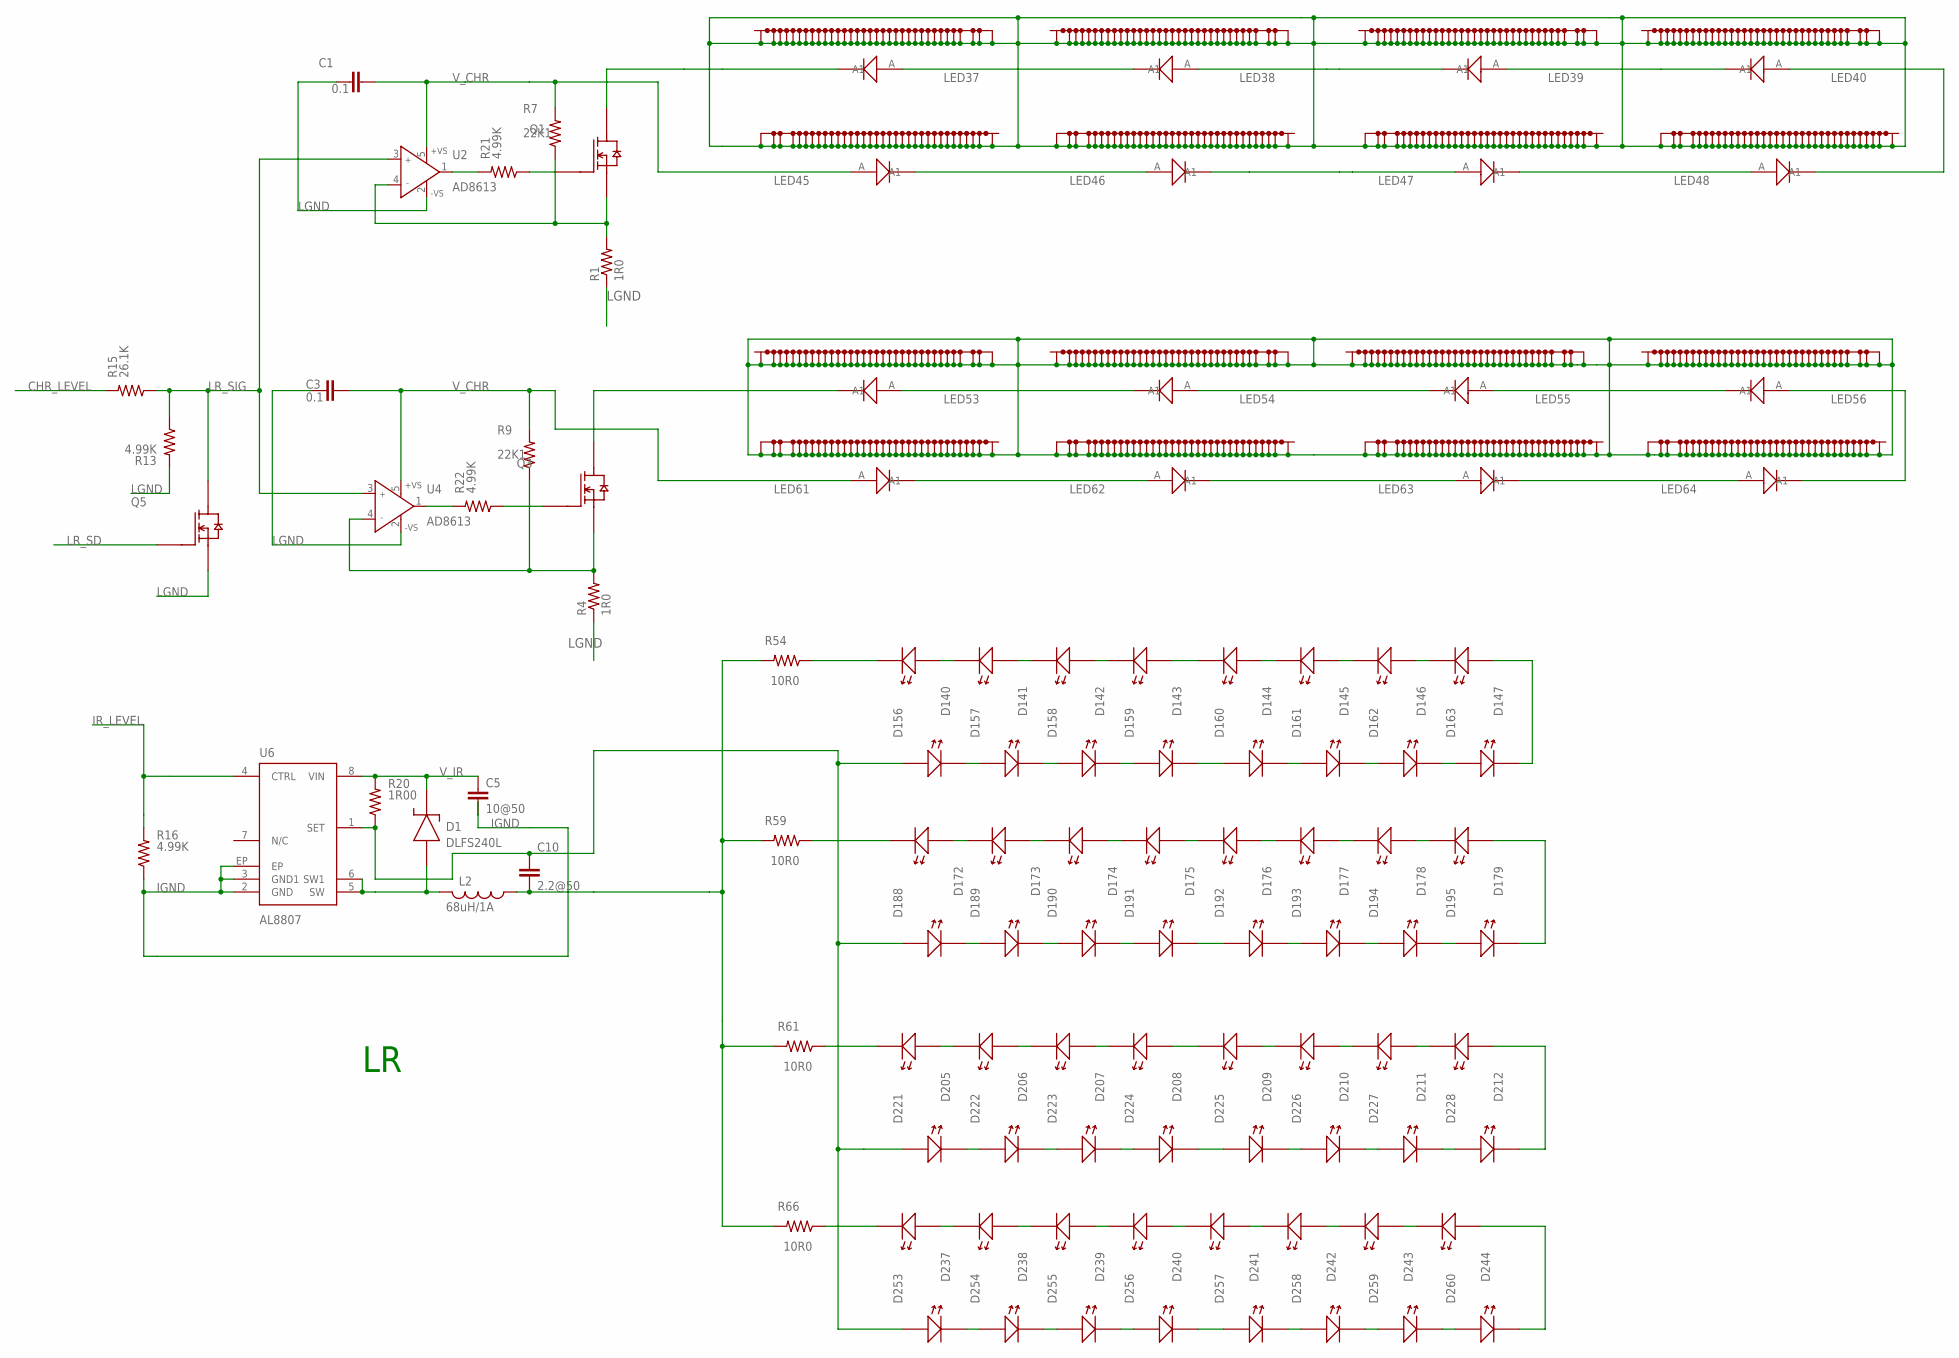
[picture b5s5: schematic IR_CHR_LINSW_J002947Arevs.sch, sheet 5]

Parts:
C1, C3: 0.1; 0603S
C5: 10@50; 1206S
C10: 2.2@50; 1206S
D1: DLFS240L; PWRDI-123
D140, D141, D142, D143, D144, D145, D146, D147, D156, D157, D158, D159, D160, D161, D162, D163, D172, D173, D174, D175, D176, D177, D178, D179, D188, D189, D190, D191, D192, D193, D194, D195, D205, D206, D207, D208, D209, D210, D211, D212, D221, D222, D223, D224, D225, D226, D227, D228, D237, D238, D239, D240, D241, D242, D243, D244, D253, D254, D255, D256, D257, D258, D259, D260: LEDLED_SFH4050_HEAT; LED_SFH4050_HEAT
L2: 68uH/1A; SRU8043
LED37, LED38, LED39, LED40, LED45, LED46, LED47, LED48, LED53, LED54, LED55, LED56, LED61, LED62, LED63, LED64: REBEL_0603OG_LED_W0603_EVEN_12; OG_LED_W0603_EVEN_12
Q1, Q3: MOSFET-NTI252_HS; TO252_HS
Q5: MOSFET-N; SC-70
R1, R4: 1R0; 2512WIDE_HS1
R7, R9: 22K1; 0805S
R13, R21, R22: 4.99K; 0603S
R15: 26.1K; 0603S
R16: 4.99K; 0805S
R20: 1R00; 1206S
R54, R59, R61, R66: 10R0; 1206S
U2, U4: AD8613; SOT23-5
U6: AL8807; MSOP8-EP

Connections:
CHR_LEVEL: R15.2; also elsewhere on the board
IGND: C5.2, R16.1, U6.2 (GND), U6.3 (GND1), U6.EP; also elsewhere on the board
IR_DRV_LR: C10.1, D156.A, D156.A1 (A), D188.A, D188.A1 (A), D221.A, D221.A1 (A), D253.A, D253.A1 (A), R20.1, U6.1 (SET)
IR_LEVEL: R16.2, U6.4 (CTRL); also elsewhere on the board
IR_RET_LR: C10.2, L2.1, R54.2, R59.2, R61.2, R66.2
LGND: C1.2, C3.2, Q5.2 (S), R1.1, R1.1A (1), R1.1A1 (1), R1.1B (1), R1.1B1 (1), R1.1C (1), R4.1, R4.1A (1), R4.1A1 (1), R4.1B (1), R4.1B1 (1), R4.1C (1), R13.2, U2.2 (-VS), U4.2 (-VS); also elsewhere on the board
LR_SD: Q5.1 (G); also elsewhere on the board
LR_SIG: Q5.3 (D), R13.1, R15.1, U2.3 (IN+), U4.3 (IN+)
unnamed: D1.A, L2.2, U6.5 (SW), U6.6 (SW1)
unnamed: Q1.1 (G), R21.1
unnamed: R21.2, U2.1 (OUT)
unnamed: Q3.2 (S), R4.2, R9.1, U4.4 (IN-)
unnamed: R22.2, U4.1 (OUT)
unnamed: Q1.2 (S), R1.2, R7.1, U2.4 (IN-)
unnamed: Q3.1 (G), R22.1
unnamed: D211.A, D211.A1 (A), D212.C (K), D212.C1 (K)
unnamed: D210.A, D210.A1 (A), D211.C (K), D211.C1 (K)
unnamed: D209.A, D209.A1 (A), D210.C (K), D210.C1 (K)
unnamed: D207.A, D207.A1 (A), D208.C (K), D208.C1 (K)
unnamed: D206.A, D206.A1 (A), D207.C (K), D207.C1 (K)
unnamed: D205.A, D205.A1 (A), D206.C (K), D206.C1 (K)
unnamed: D221.C (K), D221.C1 (K), D222.A, D222.A1 (A)
unnamed: D243.A, D243.A1 (A), D244.C (K), D244.C1 (K)
unnamed: D242.A, D242.A1 (A), D243.C (K), D243.C1 (K)
unnamed: D241.A, D241.A1 (A), D242.C (K), D242.C1 (K)
unnamed: D240.A, D240.A1 (A), D241.C (K), D241.C1 (K)
unnamed: D239.A, D239.A1 (A), D240.C (K), D240.C1 (K)
unnamed: D238.A, D238.A1 (A), D239.C (K), D239.C1 (K)
unnamed: D237.A, D237.A1 (A), D238.C (K), D238.C1 (K)
unnamed: D225.C (K), D225.C1 (K), D226.A, D226.A1 (A)
unnamed: D226.C (K), D226.C1 (K), D227.A, D227.A1 (A)
unnamed: D227.C (K), D227.C1 (K), D228.A, D228.A1 (A)
unnamed: D253.C (K), D253.C1 (K), D254.A, D254.A1 (A)
unnamed: D255.C (K), D255.C1 (K), D256.A, D256.A1 (A)
unnamed: D257.C (K), D257.C1 (K), D258.A, D258.A1 (A)
unnamed: D258.C (K), D258.C1 (K), D259.A, D259.A1 (A)
unnamed: D259.C (K), D259.C1 (K), D260.A, D260.A1 (A)
unnamed: D212.A, D212.A1 (A), D228.C (K), D228.C1 (K)
unnamed: D256.C (K), D256.C1 (K), D257.A, D257.A1 (A)
unnamed: D244.A, D244.A1 (A), D260.C (K), D260.C1 (K)
unnamed: D178.A, D178.A1 (A), D179.C (K), D179.C1 (K)
unnamed: D175.A, D175.A1 (A), D176.C (K), D176.C1 (K)
unnamed: D174.A, D174.A1 (A), D175.C (K), D175.C1 (K)
unnamed: D173.A, D173.A1 (A), D174.C (K), D174.C1 (K)
unnamed: D172.A, D172.A1 (A), D173.C (K), D173.C1 (K)
unnamed: D160.C (K), D160.C1 (K), D161.A, D161.A1 (A)
unnamed: D188.C (K), D188.C1 (K), D189.A, D189.A1 (A)
unnamed: D146.A, D146.A1 (A), D147.C (K), D147.C1 (K)
unnamed: D145.A, D145.A1 (A), D146.C (K), D146.C1 (K)
unnamed: D144.A, D144.A1 (A), D145.C (K), D145.C1 (K)
unnamed: D142.A, D142.A1 (A), D143.C (K), D143.C1 (K)
unnamed: D141.A, D141.A1 (A), D142.C (K), D142.C1 (K)
unnamed: D159.C (K), D159.C1 (K), D160.A, D160.A1 (A)
unnamed: D147.A, D147.A1 (A), D163.C (K), D163.C1 (K)
unnamed: D157.C (K), D157.C1 (K), D158.A, D158.A1 (A)
unnamed: D179.A, D179.A1 (A), D195.C (K), D195.C1 (K)
unnamed: D176.A, D176.A1 (A), D177.C (K), D177.C1 (K)
unnamed: D254.C (K), D254.C1 (K), D255.A, D255.A1 (A)
unnamed: D224.C (K), D224.C1 (K), D225.A, D225.A1 (A)
unnamed: D162.C (K), D162.C1 (K), D163.A, D163.A1 (A)
unnamed: D208.A, D208.A1 (A), D209.C (K), D209.C1 (K)
unnamed: LED63.C (K1), LED64.A (A1)
unnamed: LED56.A (A1), LED64.C (K1)
unnamed: LED53.A (A1), LED54.C (K1)
unnamed: LED54.A (A1), LED55.C (K1)
unnamed: LED55.A (A1), LED56.C (K1)
unnamed: LED47.C (K1), LED48.A (A1)
unnamed: LED40.A (A1), LED48.C (K1)
unnamed: LED46.C (K1), LED47.A (A1)
unnamed: LED45.C (K1), LED46.A (A1)
unnamed: LED38.A (A1), LED39.C (K1)
unnamed: D140.C (K), D140.C1 (K), R54.1
unnamed: D172.C (K), D172.C1 (K), R59.1
unnamed: D205.C (K), D205.C1 (K), R61.1
unnamed: D237.C (K), D237.C1 (K), R66.1
unnamed: D222.C (K), D222.C1 (K), D223.A, D223.A1 (A)
unnamed: D223.C (K), D223.C1 (K), D224.A, D224.A1 (A)
unnamed: D177.A, D177.A1 (A), D178.C (K), D178.C1 (K)
unnamed: D161.C (K), D161.C1 (K), D162.A, D162.A1 (A)
unnamed: D143.A, D143.A1 (A), D144.C (K), D144.C1 (K)
unnamed: D140.A, D140.A1 (A), D141.C (K), D141.C1 (K)
unnamed: D156.C (K), D156.C1 (K), D157.A, D157.A1 (A)
unnamed: D158.C (K), D158.C1 (K), D159.A, D159.A1 (A)
unnamed: D189.C (K), D189.C1 (K), D190.A, D190.A1 (A)
unnamed: D190.C (K), D190.C1 (K), D191.A, D191.A1 (A)
unnamed: D191.C (K), D191.C1 (K), D192.A, D192.A1 (A)
unnamed: D192.C (K), D192.C1 (K), D193.A, D193.A1 (A)
unnamed: D193.C (K), D193.C1 (K), D194.A, D194.A1 (A)
unnamed: D194.C (K), D194.C1 (K), D195.A, D195.A1 (A)
unnamed: LED62.C (K1), LED63.A (A1)
unnamed: LED61.C (K1), LED62.A (A1)
unnamed: LED37.A (A1), LED38.C (K1)
unnamed: LED39.A (A1), LED40.C (K1)
Q2: LED53.C (K1), Q3.3 (D), Q3.3S (D), Q3.P$1 (D), Q3.P$2 (D), Q3.P$3 (D), Q3.P$4 (D), Q3.P$5 (D), Q3.P$6 (D), Q3.P$7 (D), Q3.P$8 (D), Q3.P$9 (D), Q3.P$10 (D), Q3.P$11 (D), Q3.P$12 (D)
Q4: LED37.C (K1), Q1.3 (D), Q1.3S (D), Q1.P$1 (D), Q1.P$2 (D), Q1.P$3 (D), Q1.P$4 (D), Q1.P$5 (D), Q1.P$6 (D), Q1.P$7 (D), Q1.P$8 (D), Q1.P$9 (D), Q1.P$10 (D), Q1.P$11 (D), Q1.P$12 (D)
TH: LED37.TH1 (TH), LED37.TH@38 (TH), LED37.TH@39 (TH), LED37.TH@40 (TH), LED37.TH@41 (TH), LED37.TH@42 (TH), LED37.TH@43 (TH), LED37.TH@44 (TH), LED37.TH@45 (TH), LED37.TH@46 (TH), LED37.TH@47 (TH), LED37.TH@48 (TH), LED37.TH@49 (TH), LED37.TH@50 (TH), LED37.TH@51 (TH), LED37.TH@52 (TH), LED37.TH@53 (TH), LED37.TH@54 (TH), LED37.TH@55 (TH), LED37.TH@56 (TH), LED37.TH@57 (TH), LED37.TH@58 (TH), LED37.TH@59 (TH), LED37.TH@60 (TH), LED37.TH@61 (TH), LED37.TH@62 (TH), LED37.TH@63 (TH), LED37.TH@64 (TH), LED37.TH@65 (TH), LED37.TH@66 (TH), LED37.TH@67 (TH), LED37.TH@68 (TH), LED37.TH@69 (TH), LED37.TH@70 (TH), LED38.TH1 (TH), LED38.TH@38 (TH), LED38.TH@39 (TH), LED38.TH@40 (TH), LED38.TH@41 (TH), LED38.TH@42 (TH), LED38.TH@43 (TH), LED38.TH@44 (TH), LED38.TH@45 (TH), LED38.TH@46 (TH), LED38.TH@47 (TH), LED38.TH@48 (TH), LED38.TH@49 (TH), LED38.TH@50 (TH), LED38.TH@51 (TH), LED38.TH@52 (TH), LED38.TH@53 (TH), LED38.TH@54 (TH), LED38.TH@55 (TH), LED38.TH@56 (TH), LED38.TH@57 (TH), LED38.TH@58 (TH), LED38.TH@59 (TH), LED38.TH@60 (TH), LED38.TH@61 (TH), LED38.TH@62 (TH), LED38.TH@63 (TH), LED38.TH@64 (TH), LED38.TH@65 (TH), LED38.TH@66 (TH), LED38.TH@67 (TH), LED38.TH@68 (TH), LED38.TH@69 (TH), LED38.TH@70 (TH), LED39.TH1 (TH), LED39.TH@38 (TH), LED39.TH@39 (TH), LED39.TH@40 (TH), LED39.TH@41 (TH), LED39.TH@42 (TH), LED39.TH@43 (TH), LED39.TH@44 (TH), LED39.TH@45 (TH), LED39.TH@46 (TH), LED39.TH@47 (TH), LED39.TH@48 (TH), LED39.TH@49 (TH), LED39.TH@50 (TH), LED39.TH@51 (TH), LED39.TH@52 (TH), LED39.TH@53 (TH), LED39.TH@54 (TH), LED39.TH@55 (TH), LED39.TH@56 (TH), LED39.TH@57 (TH), LED39.TH@58 (TH), LED39.TH@59 (TH), LED39.TH@60 (TH), LED39.TH@61 (TH), LED39.TH@62 (TH), LED39.TH@63 (TH), LED39.TH@64 (TH), LED39.TH@65 (TH), LED39.TH@66 (TH), LED39.TH@67 (TH), LED39.TH@68 (TH), LED39.TH@69 (TH), LED39.TH@70 (TH), LED40.TH1 (TH), LED40.TH@38 (TH), LED40.TH@39 (TH), LED40.TH@40 (TH), LED40.TH@41 (TH), LED40.TH@42 (TH), LED40.TH@43 (TH), LED40.TH@44 (TH), LED40.TH@45 (TH), LED40.TH@46 (TH), LED40.TH@47 (TH), LED40.TH@48 (TH), LED40.TH@49 (TH), LED40.TH@50 (TH), LED40.TH@51 (TH), LED40.TH@52 (TH), LED40.TH@53 (TH), LED40.TH@54 (TH), LED40.TH@55 (TH), LED40.TH@56 (TH), LED40.TH@57 (TH), LED40.TH@58 (TH), LED40.TH@59 (TH), LED40.TH@60 (TH), LED40.TH@61 (TH), LED40.TH@62 (TH), LED40.TH@63 (TH), LED40.TH@64 (TH), LED40.TH@65 (TH), LED40.TH@66 (TH), LED40.TH@67 (TH), LED40.TH@68 (TH), LED40.TH@69 (TH), LED40.TH@70 (TH), LED45.TH1 (TH), LED45.TH@38 (TH), LED45.TH@39 (TH), LED45.TH@40 (TH), LED45.TH@41 (TH), LED45.TH@42 (TH), LED45.TH@43 (TH), LED45.TH@44 (TH), LED45.TH@45 (TH), LED45.TH@46 (TH), LED45.TH@47 (TH), LED45.TH@48 (TH), LED45.TH@49 (TH), LED45.TH@50 (TH), LED45.TH@51 (TH), LED45.TH@52 (TH), LED45.TH@53 (TH), LED45.TH@54 (TH), LED45.TH@55 (TH), LED45.TH@56 (TH), LED45.TH@57 (TH), LED45.TH@58 (TH), LED45.TH@59 (TH), LED45.TH@60 (TH), LED45.TH@61 (TH), LED45.TH@62 (TH), LED45.TH@63 (TH), LED45.TH@64 (TH), LED45.TH@65 (TH), LED45.TH@66 (TH), LED45.TH@67 (TH), LED45.TH@68 (TH), LED45.TH@69 (TH), LED45.TH@70 (TH), LED46.TH1 (TH), LED46.TH@38 (TH), LED46.TH@39 (TH), LED46.TH@40 (TH), LED46.TH@41 (TH), LED46.TH@42 (TH), LED46.TH@43 (TH), LED46.TH@44 (TH), LED46.TH@45 (TH), LED46.TH@46 (TH), LED46.TH@47 (TH), LED46.TH@48 (TH), LED46.TH@49 (TH), LED46.TH@50 (TH), LED46.TH@51 (TH), LED46.TH@52 (TH), LED46.TH@53 (TH), LED46.TH@54 (TH), LED46.TH@55 (TH), LED46.TH@56 (TH), LED46.TH@57 (TH), LED46.TH@58 (TH), LED46.TH@59 (TH), LED46.TH@60 (TH), LED46.TH@61 (TH), LED46.TH@62 (TH), LED46.TH@63 (TH), LED46.TH@64 (TH)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; also elsewhere on the board
V_CHR: C1.1, C3.1, LED45.A (A1), LED61.A (A1), R7.2, R9.2, U2.5 (+VS), U4.5 (+VS); also elsewhere on the board
V_IR: C5.1, D1.K, R20.2, U6.8 (VIN); also elsewhere on the board
